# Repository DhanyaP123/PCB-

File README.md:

AC TO DC CONVERTOR 

An AC to DC converter, also called a rectifier, is an electronic device that converts alternating current (AC) — the kind of current supplied by your wall outlet — into direct current (DC), which is required by most electronic devices like:

Mobile phones

Laptops

LEDs

Microcontrollers

Power banks

---

Why is it needed?

AC voltage changes direction (polarity) constantly, while DC voltage flows in one direction only. Most electronic components (like chips, sensors, etc.) can only work with DC. So, the converter ensures the devices get the steady, one-way flow of electricity they need.

---

EXAMPLE 

If you use a mobile phone charger, it takes 230V AC from the wall and gives out something like 5V DC to charge your phone. That’s a real-world AC to DC converter.

---

COMPONENTS 

i)  4 IN4007 diode.

ii) 2 resistors(10k and 2.2k)

iii)2 screw terminals

iv) 1 capacitor (1000uF)

v)  1 LED

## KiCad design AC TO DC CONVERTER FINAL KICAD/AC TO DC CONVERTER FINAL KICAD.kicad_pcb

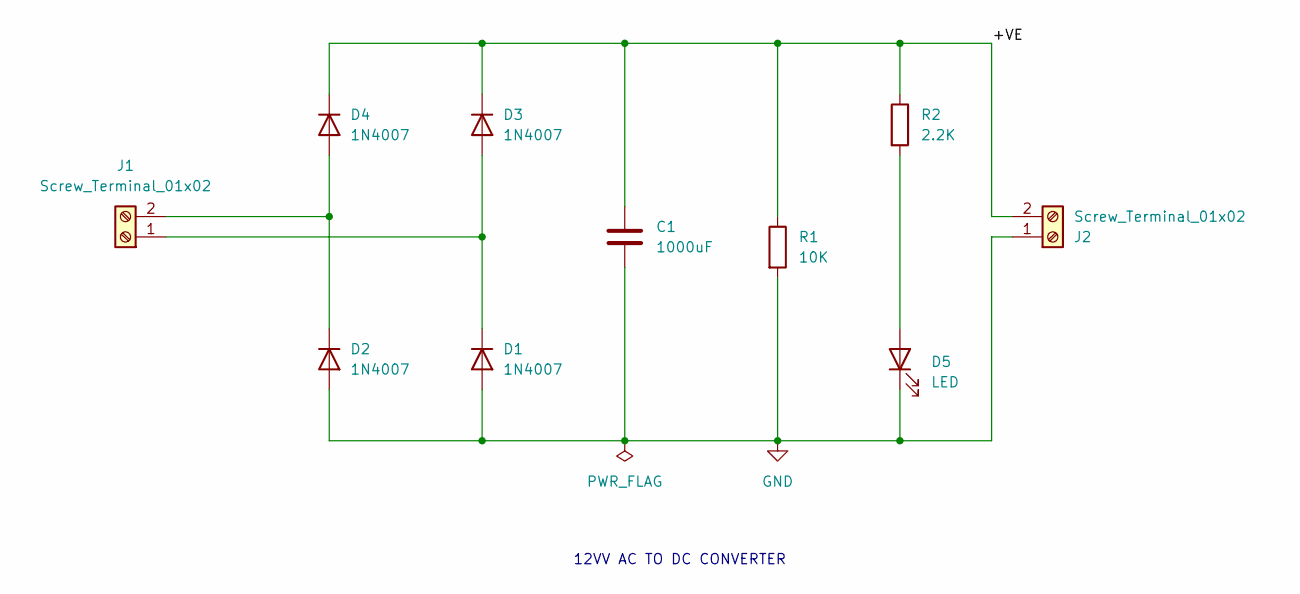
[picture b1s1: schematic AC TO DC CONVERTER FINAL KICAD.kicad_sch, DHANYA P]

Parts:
C1: 1000uF; C_Radial_D8.0mm_H11.5mm_P3.50mm
D1, D2, D3, D4: 1N4007; D_DO-41_SOD81_P10.16mm_Horizontal
D5: LED; LED_D5.0mm
J1, J2: Screw_Terminal_01x02; TerminalBlock_bornier-2_P5.08mm
R1: 10K; R_Axial_DIN0207_L6.3mm_D2.5mm_P7.62mm_Horizontal
R2: 2.2K; R_Axial_DIN0207_L6.3mm_D2.5mm_P7.62mm_Horizontal

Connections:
/+VE: C1.1, D3.1 (K), D4.1 (K), J2.2, R1.1, R2.1
GND: C1.2, D1.2 (A), D2.2 (A), D5.1 (K), J2.1, R1.2
unnamed: D1.1 (K), D3.2 (A), J1.1
unnamed: D2.1 (K), D4.2 (A), J1.2
unnamed: D5.2 (A), R2.2

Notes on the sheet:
12VV AC TO DC CONVERTER

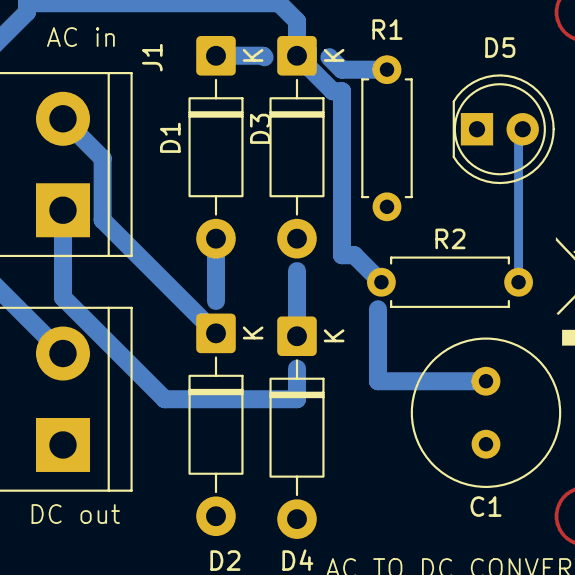
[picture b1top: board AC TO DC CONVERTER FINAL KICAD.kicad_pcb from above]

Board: 2 copper layers, 10 parts (0 on the bottom side), 5 nets.
